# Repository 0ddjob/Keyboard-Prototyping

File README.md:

# Keyboard Prototyping
Prototyping boards to aid with keyboard design testing

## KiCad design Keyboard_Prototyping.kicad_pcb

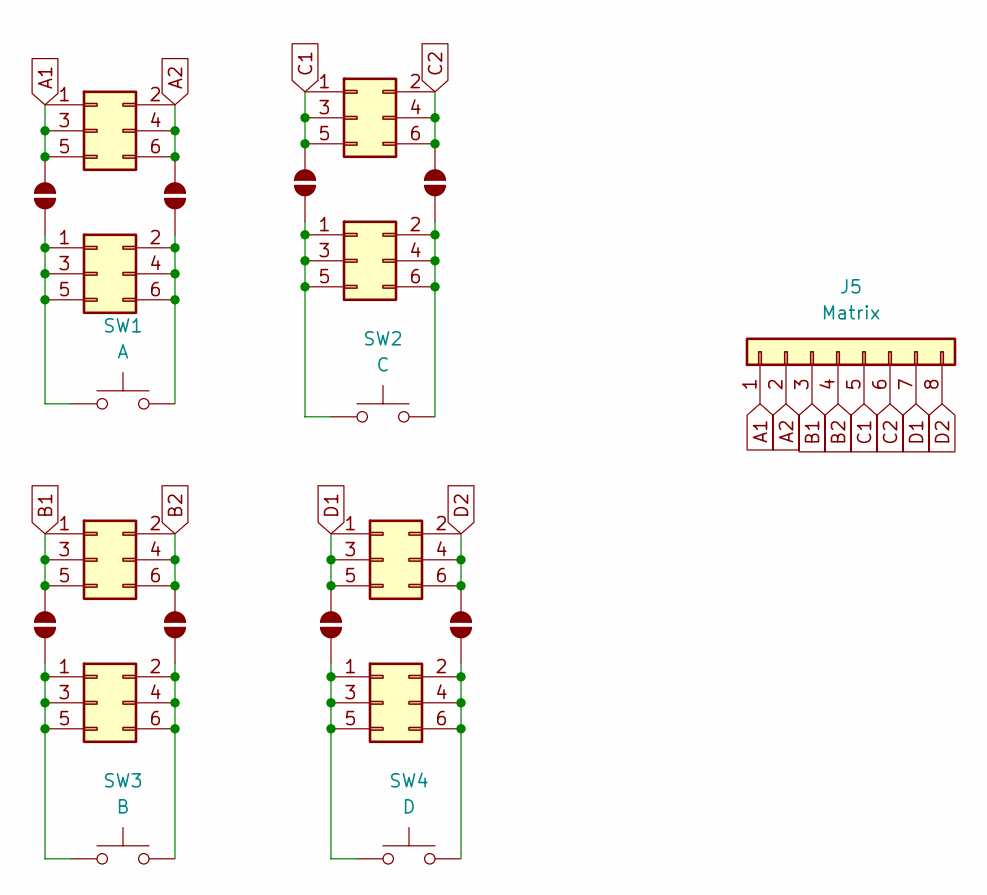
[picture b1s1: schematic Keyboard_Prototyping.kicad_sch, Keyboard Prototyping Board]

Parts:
J1, J2, J3, J4, J6, J7, J8, J18: Conn_02x03_Odd_Even; PinHeader_2x03_P2.54mm_Vertical
J5: Matrix; PinHeader_1x08_P2.54mm_Vertical
JP1, JP2, JP3, JP4, JP5, JP6, JP7, JP8: SolderJumper_2_Open; SolderJumper-2_P1.3mm_Bridged_RoundedPad1.0x1.5mm
SW1: A; SW_Cherry_MX_PCB_1.00u
SW2: C; SW_Cherry_MX_PCB_1.00u
SW3: B; SW_Cherry_MX_PCB_1.00u
SW4: D; SW_Cherry_MX_PCB_1.00u

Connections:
A1: J1.1, J1.3, J1.5, J5.1, JP1.2 (B)
A2: J1.2, J1.4, J1.6, J5.2, JP2.2 (B)
B1: J4.1, J4.3, J4.5, J5.3, JP5.2 (B)
B2: J4.2, J4.4, J4.6, J5.4, JP6.2 (B)
C1: J2.1, J2.3, J2.5, J5.5, JP3.2 (B)
C2: J2.2, J2.4, J2.6, J5.6, JP4.2 (B)
D1: J5.7, J7.1, J7.3, J7.5, JP7.2 (B)
D2: J5.8, J7.2, J7.4, J7.6, JP8.2 (B)
unnamed: J3.1, J3.3, J3.5, JP3.1 (A), SW2.1
unnamed: J3.2, J3.4, J3.6, JP4.1 (A), SW2.2
unnamed: J6.1, J6.3, J6.5, JP5.1 (A), SW3.1
unnamed: J6.2, J6.4, J6.6, JP6.1 (A), SW3.2
unnamed: J8.1, J8.3, J8.5, JP7.1 (A), SW4.1
unnamed: J8.2, J8.4, J8.6, JP8.1 (A), SW4.2
unnamed: J18.1, J18.3, J18.5, JP1.1 (A), SW1.1
unnamed: J18.2, J18.4, J18.6, JP2.1 (A), SW1.2

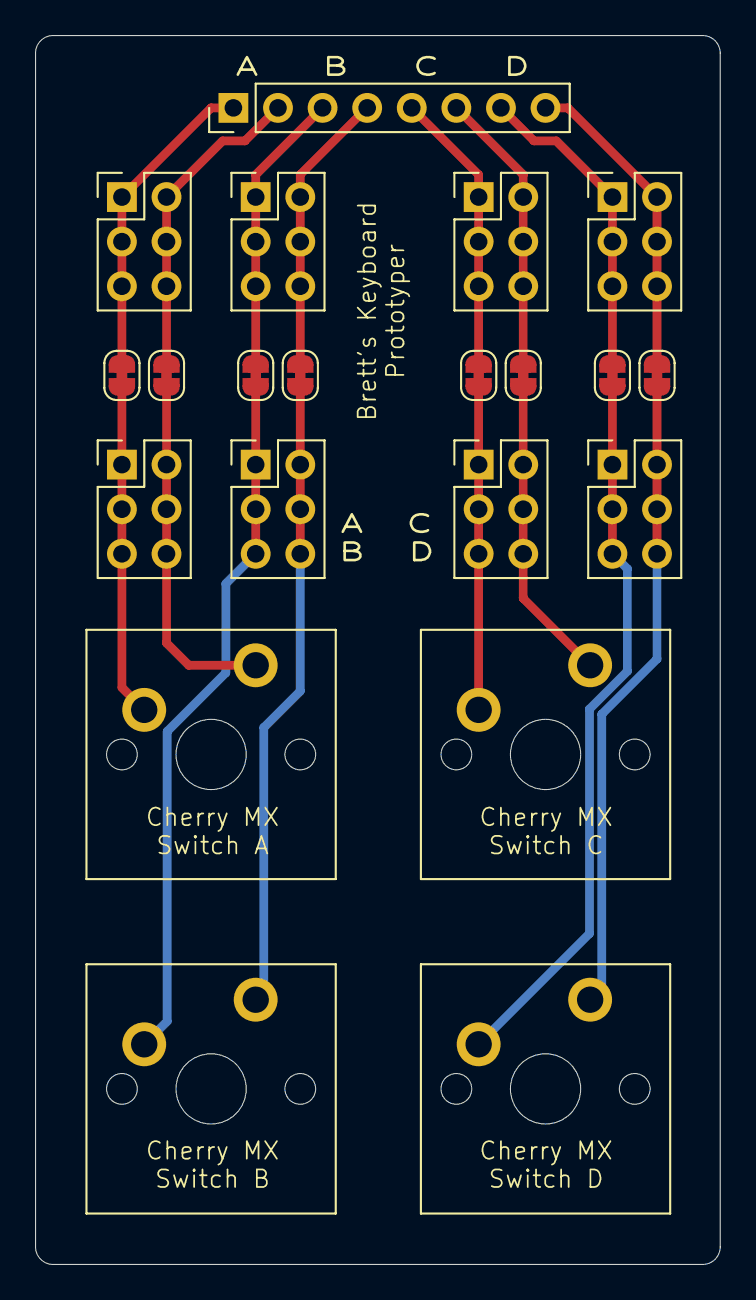
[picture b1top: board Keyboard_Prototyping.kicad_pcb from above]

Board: 2 copper layers, 39.0 x 70.0 mm, 21 parts (0 on the bottom side), 16 nets.

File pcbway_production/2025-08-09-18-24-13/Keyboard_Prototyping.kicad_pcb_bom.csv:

Designator,Quantity,Value,Footprint,Package,MPN,DNP,Mount_Type,Description
"J1, J18, J2, J3, J4, J6, J7, J8",8,Conn_02x03_Odd_Even,PinHeader_2x03_P2.54mm_Vertical,,,,tht,"Generic connector, double row, 02x03, odd/even pin numbering scheme (row 1 odd numbers, row 2 even numbers), script generated (kicad-library-utils/schlib/autogen/connector/)"
J5,1,Conn_01x08,PinHeader_1x08_P2.54mm_Vertical,,,,tht,"Generic connector, single row, 01x08, script generated (kicad-library-utils/schlib/autogen/connector/)"
SW1,1,A,SW_Cherry_MX_PCB_1.00u,,,,tht,"Push button switch, generic, two pins"
SW2,1,C,SW_Cherry_MX_PCB_1.00u,,,,tht,"Push button switch, generic, two pins"
SW3,1,B,SW_Cherry_MX_PCB_1.00u,,,,tht,"Push button switch, generic, two pins"
SW4,1,D,SW_Cherry_MX_PCB_1.00u,,,,tht,"Push button switch, generic, two pins"

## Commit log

2025-08-09 Generated fabrication files
